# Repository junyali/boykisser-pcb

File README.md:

# Boykisser PCB

@junya
A small hardware project with some basic parts, cut in the shape of a Boykisser :3
PCB with a couple of clicky tactile buttons that lights up some LEDS.

## BOM

- 1x CR2032 Battery Holder (Keystone_3034_1x20mm)
- 3x LEDs 5.0mm (THT)
- 1x Mini vibrator motor disc
- 3x 220Ω Resistors (THT)
- 3x Button Switch Push 6.0mm (THT)

## Concept

| Demo             |                    Image                     |
|------------------|:--------------------------------------------:|
| Schematic        |            |
| PCB Design       |                 |
| PCB Front Render |  |
| PCB Back Render  |    |

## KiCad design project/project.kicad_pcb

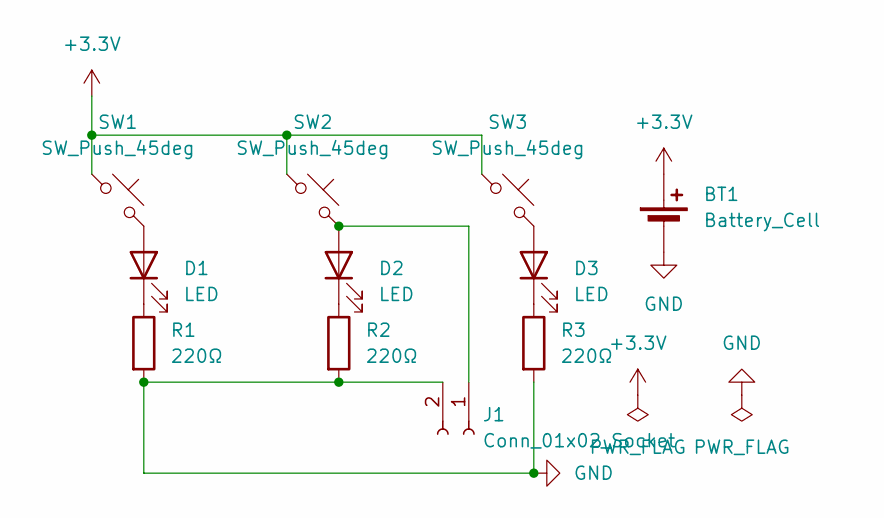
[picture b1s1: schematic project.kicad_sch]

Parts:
BT1: Battery_Cell; BatteryHolder_Keystone_3034_1x20mm
D1, D2, D3: LED; LED_D5.0mm
J1: Conn_01x02_Socket; PinHeader_1x02_P2.54mm_Vertical
R1, R2, R3: 220Ω; R_Axial_DIN0207_L6.3mm_D2.5mm_P7.62mm_Horizontal
SW1, SW2, SW3: SW_Push_45deg; SW_PUSH_6mm

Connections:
+3.3V: BT1.1 (+), SW1.1, SW2.1, SW3.1
GND: BT1.2 (-), J1.2, R1.2, R2.2, R3.2
unnamed: D1.2 (A), SW1.2
unnamed: D1.1 (K), R1.1
unnamed: D2.2 (A), J1.1, SW2.2
unnamed: D2.1 (K), R2.1
unnamed: D3.2 (A), SW3.2
unnamed: D3.1 (K), R3.1

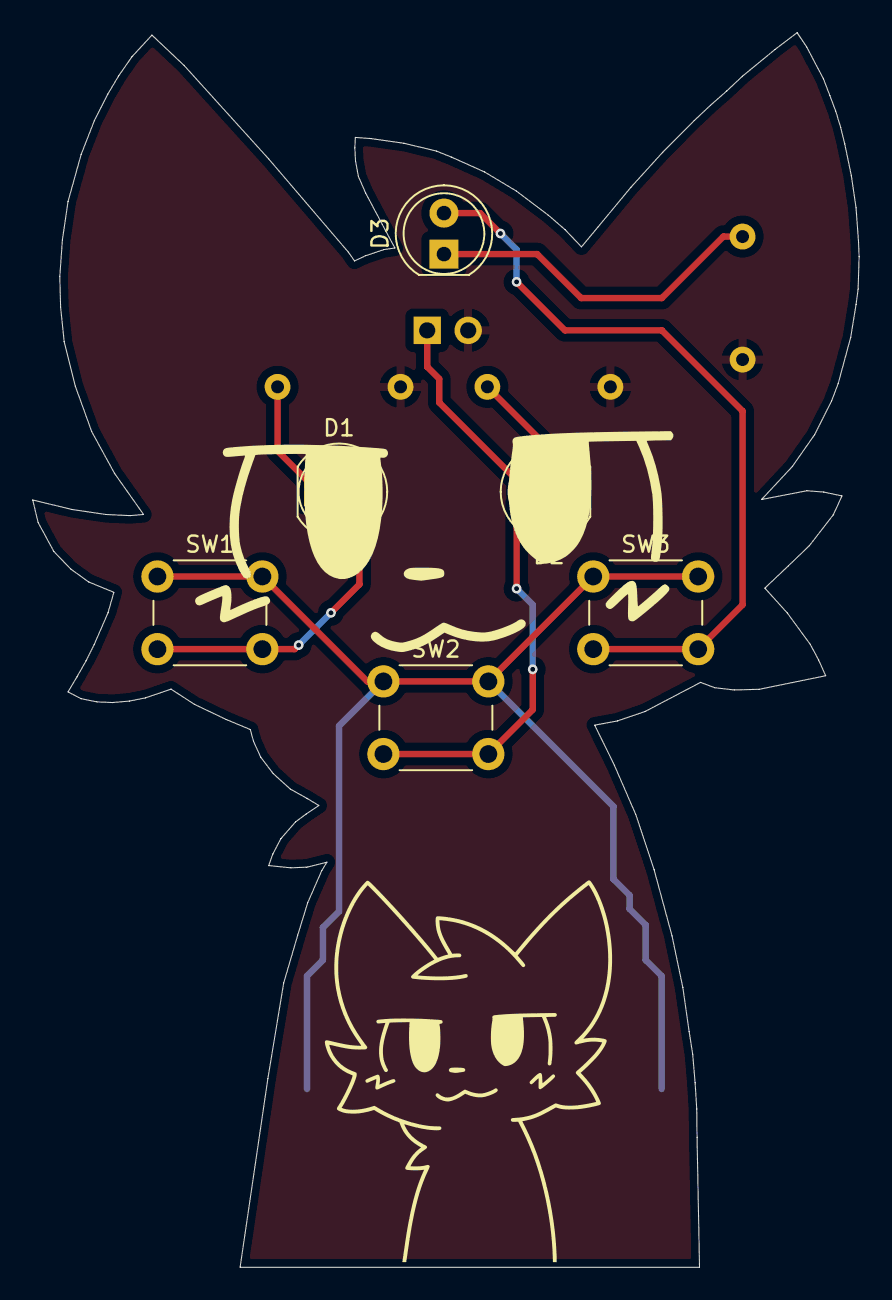
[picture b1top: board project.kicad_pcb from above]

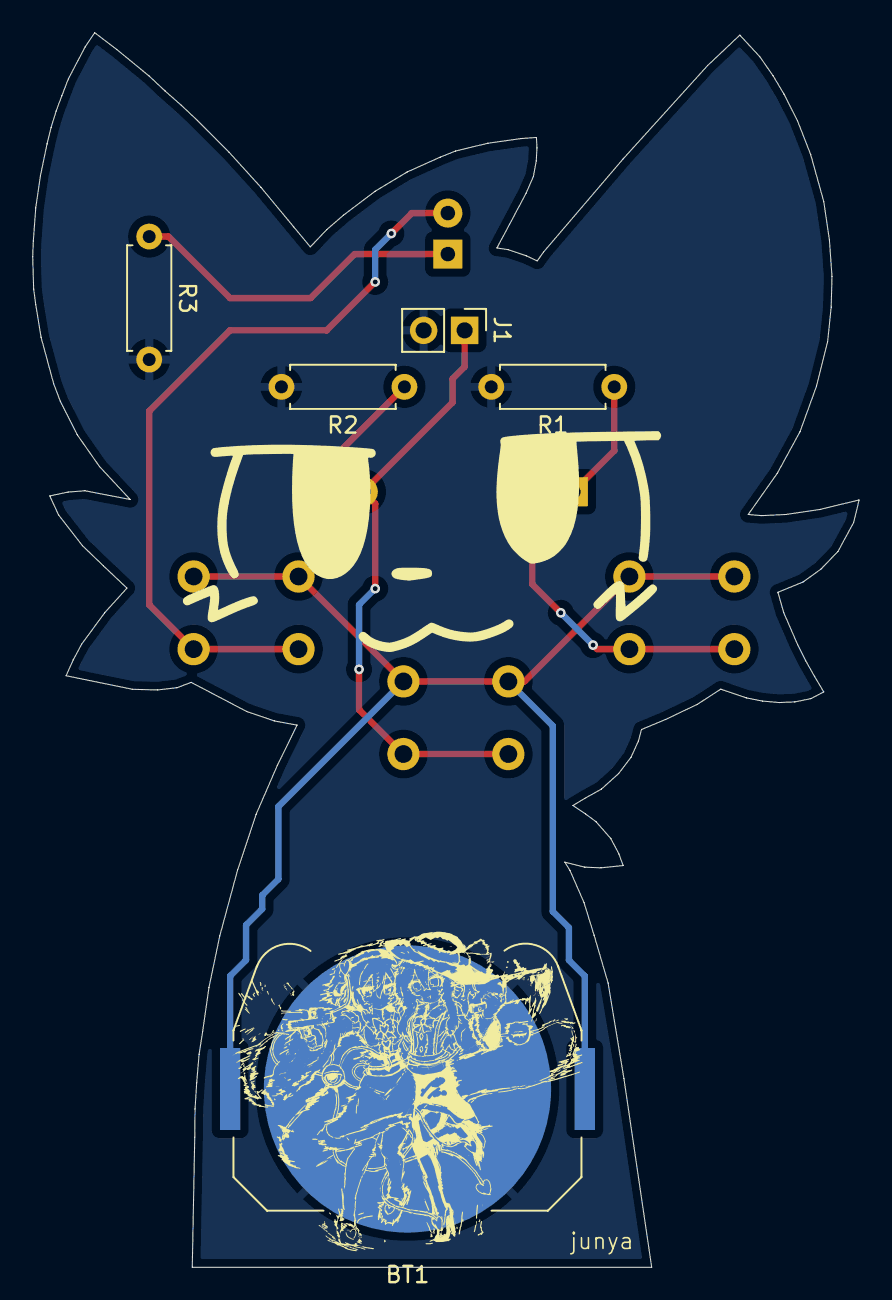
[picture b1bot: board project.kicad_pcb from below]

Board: 2 copper layers, 51.2 x 76.5 mm, 11 parts (5 on the bottom side), 8 nets.

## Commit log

2025-04-08 Add .gitignore
2025-04-08 Remove reference drawing
2025-04-08 Add gerbers
2025-04-09 Add README.md
2025-04-10 Put component in parallel
